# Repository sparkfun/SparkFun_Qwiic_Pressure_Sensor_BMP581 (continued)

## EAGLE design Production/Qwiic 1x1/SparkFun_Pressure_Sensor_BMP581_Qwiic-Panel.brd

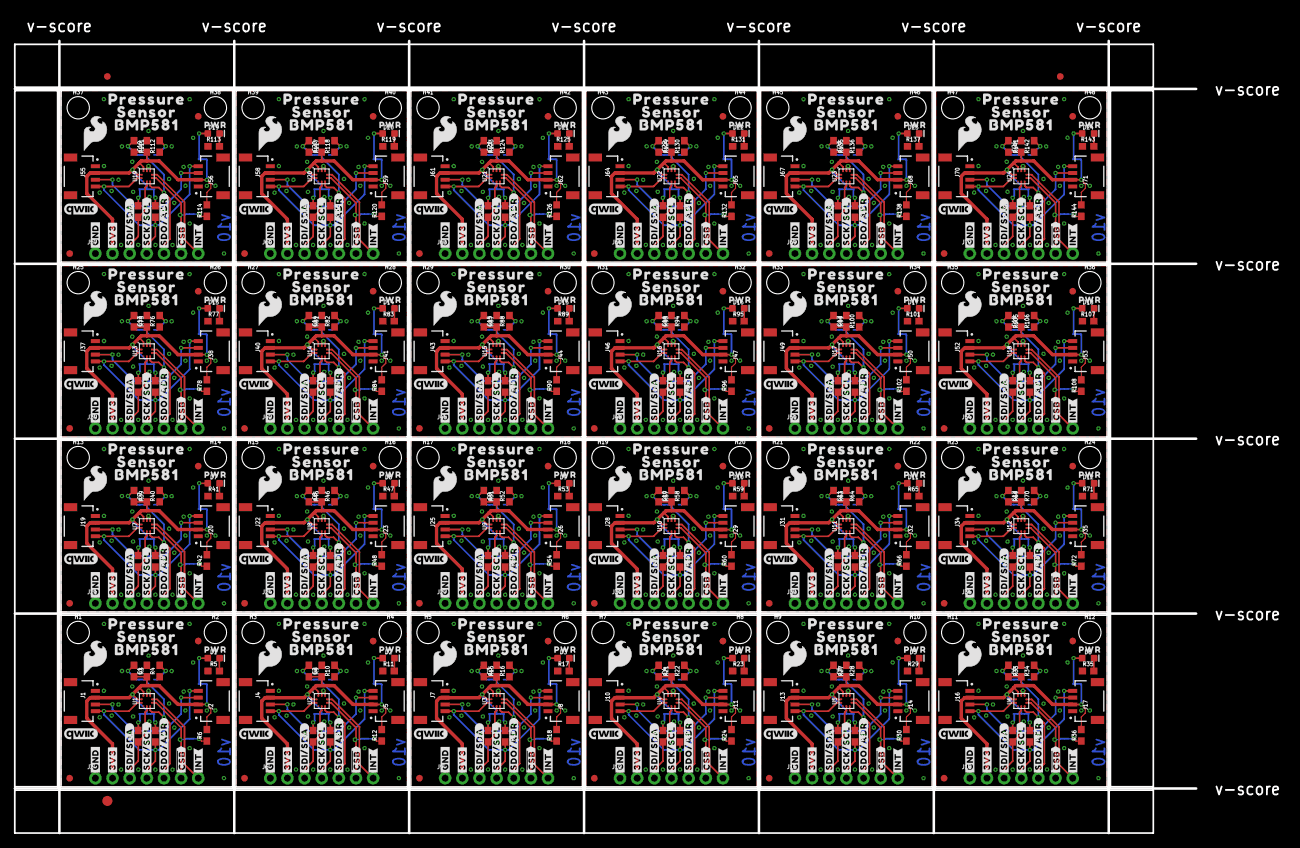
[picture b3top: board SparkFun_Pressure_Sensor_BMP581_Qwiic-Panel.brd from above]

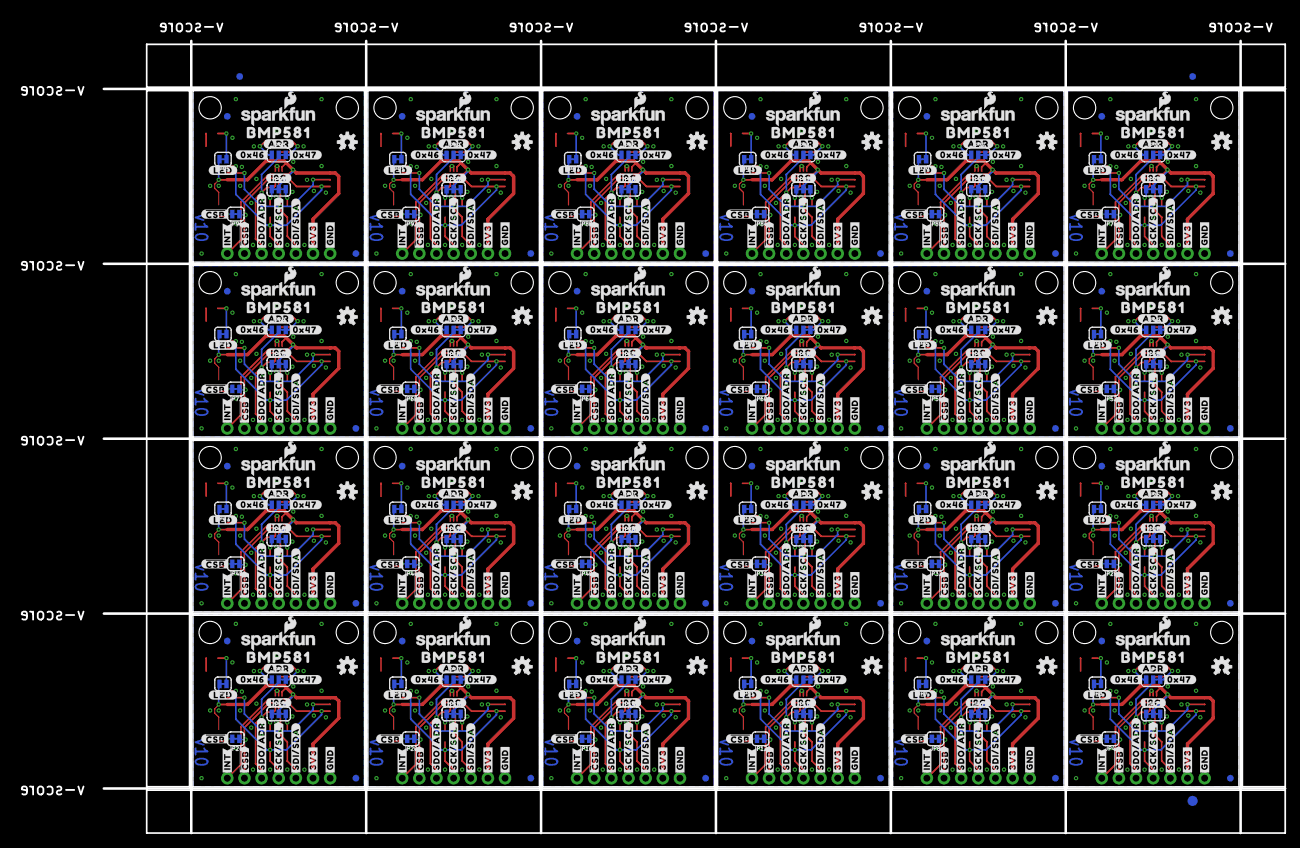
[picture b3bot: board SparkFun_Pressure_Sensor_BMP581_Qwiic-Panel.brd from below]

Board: 2 copper layers, 175.0 x 117.3 mm, 1230 parts (531 on the bottom side), 336 nets.

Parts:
C1, C2, C3, C4, C5, C6, C7, C8, C9, C10, C11, C12, C13, C14, C15, C16, C17, C18, C19, C20, C21, C22, C23, C24: 0.1uF; 0603
D1, D2, D3, D4, D5, D6, D7, D8, D9, D10, D11, D12, D13, D14, D15, D16, D17, D18, D19, D20, D21, D22, D23, D24: RED; LED-0603
E$1, E$2, E$3, E$4: FIDUCIAL-1X2
E$5, E$6: FIDUCIAL-1.5X3
FD1, FD2, FD3, FD4, FD5, FD6, FD7, FD8, FD9, FD10, FD11, FD12, FD13, FD14, FD15, FD16, FD17, FD18, FD19, FD20, FD21, FD22, FD23, FD24, FD25, FD26, FD27, FD28, FD29, FD30, FD31, FD32, FD33, FD34, FD35, FD36, FD37, FD38, FD39, FD40, FD41, FD42, FD43, FD44, FD45, FD46, FD47, FD48, FD49, FD50, FD51, FD52, FD53, FD54, FD55, FD56, FD57, FD58, FD59, FD60, FD61, FD62, FD63, FD64, FD65, FD66, FD67, FD68, FD69, FD70, FD71, FD72, FD73, FD74, FD75, FD76, FD77, FD78, FD79, FD80, FD81, FD82, FD83, FD84, FD85, FD86, FD87, FD88, FD89, FD90, FD91, FD92, FD93, FD94, FD95, FD96: FIDUCIAL1X2; FIDUCIAL-1X2
H1, H2, H3, H4, H5, H6, H7, H8, H9, H10, H11, H12, H13, H14, H15, H16, H17, H18, H19, H20, H21, H22, H23, H24, H25, H26, H27, H28, H29, H30, H31, H32, H33, H34, H35, H36, H37, H38, H39, H40, H41, H42, H43, H44, H45, H46, H47, H48: STAND-OFF
J1, J2, J4, J5, J7, J8, J10, J11, J13, J14, J16, J17, J19, J20, J22, J23, J25, J26, J28, J29, J31, J32, J34, J35, J37, J38, J40, J41, J43, J44, J46, J47, J49, J50, J52, J53, J55, J56, J58, J59, J61, J62, J64, J65, J67, J68, J70, J71: QWIIC_RIGHT_ANGLE; JST04_1MM_RA
J3, J6, J9, J12, J15, J18, J21, J24, J27, J30, J33, J36, J39, J42, J45, J48, J51, J54, J57, J60, J63, J66, J69, J72: 1X07_NO_SILK
JP1, JP5, JP9, JP13, JP17, JP21, JP25, JP29, JP33, JP37, JP41, JP45, JP49, JP53, JP57, JP61, JP65, JP69, JP73, JP77, JP81, JP85, JP89, JP93: ADR; SMT-JUMPER_3_1-NC_TRACE_SILK
JP2, JP6, JP10, JP14, JP18, JP22, JP26, JP30, JP34, JP38, JP42, JP46, JP50, JP54, JP58, JP62, JP66, JP70, JP74, JP78, JP82, JP86, JP90, JP94: I2C; SMT-JUMPER_3_2-NC_TRACE_SILK
JP3, JP7, JP11, JP15, JP19, JP23, JP27, JP31, JP35, JP39, JP43, JP47, JP51, JP55, JP59, JP63, JP67, JP71, JP75, JP79, JP83, JP87, JP91, JP95: LED; SMT-JUMPER_2_NC_TRACE_SILK
JP4, JP8, JP12, JP16, JP20, JP24, JP28, JP32, JP36, JP40, JP44, JP48, JP52, JP56, JP60, JP64, JP68, JP72, JP76, JP80, JP84, JP88, JP92, JP96: !CSB!; SMT-JUMPER_2_NC_TRACE_SILK
LOGO1, LOGO5, LOGO9, LOGO13, LOGO17, LOGO21, LOGO25, LOGO29, LOGO33, LOGO37, LOGO41, LOGO45, LOGO49, LOGO53, LOGO57, LOGO61, LOGO65, LOGO69, LOGO73, LOGO77, LOGO81, LOGO85, LOGO89, LOGO93: OSHW-LOGOS; OSHW-LOGO-S
LOGO2, LOGO6, LOGO10, LOGO14, LOGO18, LOGO22, LOGO26, LOGO30, LOGO34, LOGO38, LOGO42, LOGO46, LOGO50, LOGO54, LOGO58, LOGO62, LOGO66, LOGO70, LOGO74, LOGO78, LOGO82, LOGO86, LOGO90, LOGO94: SFE_LOGO_FLAME.2_INCH; SFE_LOGO_FLAME_.2
LOGO3, LOGO7, LOGO11, LOGO15, LOGO19, LOGO23, LOGO27, LOGO31, LOGO35, LOGO39, LOGO43, LOGO47, LOGO51, LOGO55, LOGO59, LOGO63, LOGO67, LOGO71, LOGO75, LOGO79, LOGO83, LOGO87, LOGO91, LOGO95: QWIIC_LOGO_5MM; QWIIC_5MM
LOGO4, LOGO8, LOGO12, LOGO16, LOGO20, LOGO24, LOGO28, LOGO32, LOGO36, LOGO40, LOGO44, LOGO48, LOGO52, LOGO56, LOGO60, LOGO64, LOGO68, LOGO72, LOGO76, LOGO80, LOGO84, LOGO88, LOGO92, LOGO96: SFE_LOGO_NAME_FLAME.1_INCH; SFE_LOGO_NAME_FLAME_.1
R1, R2, R7, R8, R13, R14, R19, R20, R25, R26, R31, R32, R37, R38, R43, R44, R49, R50, R55, R56, R61, R62, R67, R68, R73, R74, R79, R80, R85, R86, R91, R92, R97, R98, R103, R104, R109, R110, R115, R116, R121, R122, R127, R128, R133, R134, R139, R140: 2.2k; 0603
R3, R4, R6, R9, R10, R12, R15, R16, R18, R21, R22, R24, R27, R28, R30, R33, R34, R36, R39, R40, R42, R45, R46, R48, R51, R52, R54, R57, R58, R60, R63, R64, R66, R69, R70, R72, R75, R76, R78, R81, R82, R84, R87, R88, R90, R93, R94, R96, R99, R100, R102, R105, R106, R108, R111, R112, R114, R117, R118, R120, R123, R124, R126, R129, R130, R132, R135, R136, R138, R141, R142, R144: 10k; 0603
R5, R11, R17, R23, R29, R35, R41, R47, R53, R59, R65, R71, R77, R83, R89, R95, R101, R107, R113, R119, R125, R131, R137, R143: 1k; 0603
U1, U2, U3, U4, U5, U6, U7, U8, U9, U10, U11, U12, U13, U14, U15, U16, U17, U18, U19, U20, U21, U22, U23, U24: BMP581
U$1, U$22, U$27, U$50, U$53, U$75, U$78, U$100, U$103, U$125, U$128, U$150, U$153, U$175, U$178, U$200, U$203, U$225, U$228, U$250, U$253, U$275, U$278, U$300, U$303, U$325, U$328, U$350, U$353, U$375, U$378, U$400, U$403, U$425, U$428, U$450, U$453, U$475, U$478, U$500, U$503, U$525, U$528, U$550, U$553, U$575, U$578, U$600: BMP5810
U$2, U$3, U$29, U$30, U$54, U$55, U$79, U$80, U$104, U$105, U$129, U$130, U$154, U$155, U$179, U$180, U$204, U$205, U$229, U$230, U$254, U$255, U$279, U$280, U$304, U$305, U$329, U$330, U$354, U$355, U$379, U$380, U$404, U$405, U$429, U$430, U$454, U$455, U$479, U$480, U$504, U$505, U$529, U$530, U$554, U$555, U$579, U$580: #GND#0
U$4, U$20, U$39, U$40, U$64, U$65, U$89, U$90, U$114, U$115, U$139, U$140, U$164, U$165, U$189, U$190, U$214, U$215, U$239, U$240, U$264, U$265, U$289, U$290, U$314, U$315, U$339, U$340, U$364, U$365, U$389, U$390, U$414, U$415, U$439, U$440, U$464, U$465, U$489, U$490, U$514, U$515, U$539, U$540, U$564, U$565, U$589, U$590: #3V3#0
U$5, U$6, U$31, U$32, U$56, U$57, U$81, U$82, U$106, U$107, U$131, U$132, U$156, U$157, U$181, U$182, U$206, U$207, U$231, U$232, U$256, U$257, U$281, U$282, U$306, U$307, U$331, U$332, U$356, U$357, U$381, U$382, U$406, U$407, U$431, U$432, U$456, U$457, U$481, U$482, U$506, U$507, U$531, U$532, U$556, U$557, U$581, U$582: #SDI#SDA#0
U$7, U$8, U$33, U$34, U$58, U$59, U$83, U$84, U$108, U$109, U$133, U$134, U$158, U$159, U$183, U$184, U$208, U$209, U$233, U$234, U$258, U$259, U$283, U$284, U$308, U$309, U$333, U$334, U$358, U$359, U$383, U$384, U$408, U$409, U$433, U$434, U$458, U$459, U$483, U$484, U$508, U$509, U$533, U$534, U$558, U$559, U$583, U$584: #SCK#SCL#0
U$9, U$10, U$35, U$36, U$60, U$61, U$85, U$86, U$110, U$111, U$135, U$136, U$160, U$161, U$185, U$186, U$210, U$211, U$235, U$236, U$260, U$261, U$285, U$286, U$310, U$311, U$335, U$336, U$360, U$361, U$385, U$386, U$410, U$411, U$435, U$436, U$460, U$461, U$485, U$486, U$510, U$511, U$535, U$536, U$560, U$561, U$585, U$586: #SDO#ADR#0
U$11, U$45, U$70, U$95, U$120, U$145, U$170, U$195, U$220, U$245, U$270, U$295, U$320, U$345, U$370, U$395, U$420, U$445, U$470, U$495, U$520, U$545, U$570, U$595: #I2C#0
U$12, U$46, U$71, U$96, U$121, U$146, U$171, U$196, U$221, U$246, U$271, U$296, U$321, U$346, U$371, U$396, U$421, U$446, U$471, U$496, U$521, U$546, U$571, U$596: #0X46#0
U$13, U$14, U$37, U$38, U$62, U$63, U$87, U$88, U$112, U$113, U$137, U$138, U$162, U$163, U$187, U$188, U$212, U$213, U$237, U$238, U$262, U$263, U$287, U$288, U$312, U$313, U$337, U$338, U$362, U$363, U$387, U$388, U$412, U$413, U$437, U$438, U$462, U$463, U$487, U$488, U$512, U$513, U$537, U$538, U$562, U$563, U$587, U$588: #INT#0
U$15, U$47, U$72, U$97, U$122, U$147, U$172, U$197, U$222, U$247, U$272, U$297, U$322, U$347, U$372, U$397, U$422, U$447, U$472, U$497, U$522, U$547, U$572, U$597: #0X47#0
U$16, U$48, U$73, U$98, U$123, U$148, U$173, U$198, U$223, U$248, U$273, U$298, U$323, U$348, U$373, U$398, U$423, U$448, U$473, U$498, U$523, U$548, U$573, U$598: PWR0
U$17, U$43, U$68, U$93, U$118, U$143, U$168, U$193, U$218, U$243, U$268, U$293, U$318, U$343, U$368, U$393, U$418, U$443, U$468, U$493, U$518, U$543, U$568, U$593: #ADR#0
U$18, U$49, U$74, U$99, U$124, U$149, U$174, U$199, U$224, U$249, U$274, U$299, U$324, U$349, U$374, U$399, U$424, U$449, U$474, U$499, U$524, U$549, U$574, U$599: ##CSB##1
U$19, U$44, U$69, U$94, U$119, U$144, U$169, U$194, U$219, U$244, U$269, U$294, U$319, U$344, U$369, U$394, U$419, U$444, U$469, U$494, U$519, U$544, U$569, U$594: #LED#0
U$21, U$23, U$51, U$76, U$101, U$126, U$151, U$176, U$201, U$226, U$251, U$276, U$301, U$326, U$351, U$376, U$401, U$426, U$451, U$476, U$501, U$526, U$551, U$576: PRESSURE0
U$24, U$26, U$52, U$77, U$102, U$127, U$152, U$177, U$202, U$227, U$252, U$277, U$302, U$327, U$352, U$377, U$402, U$427, U$452, U$477, U$502, U$527, U$552, U$577: SENSOR0
U$25, U$28, U$41, U$42, U$66, U$67, U$91, U$92, U$116, U$117, U$141, U$142, U$166, U$167, U$191, U$192, U$216, U$217, U$241, U$242, U$266, U$267, U$291, U$292, U$316, U$317, U$341, U$342, U$366, U$367, U$391, U$392, U$416, U$417, U$441, U$442, U$466, U$467, U$491, U$492, U$516, U$517, U$541, U$542, U$566, U$567, U$591, U$592: ##CSB##0

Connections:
!CSB!: J3.6, JP4.1, U1.6
!CSB!1: J6.6, JP8.1, U2.6
!CSB!2: J9.6, JP12.1, U3.6
!CSB!3: J12.6, JP16.1, U4.6
!CSB!4: J15.6, JP20.1, U5.6
!CSB!5: J18.6, JP24.1, U6.6
!CSB!6: J21.6, JP28.1, U7.6
!CSB!7: J24.6, JP32.1, U8.6
!CSB!8: J27.6, JP36.1, U9.6
!CSB!9: J30.6, JP40.1, U10.6
!CSB!10: J33.6, JP44.1, U11.6
!CSB!11: J36.6, JP48.1, U12.6
!CSB!12: J39.6, JP52.1, U13.6
!CSB!13: J42.6, JP56.1, U14.6
!CSB!14: J45.6, JP60.1, U15.6
!CSB!15: J48.6, JP64.1, U16.6
!CSB!16: J51.6, JP68.1, U17.6
!CSB!17: J54.6, JP72.1, U18.6
!CSB!18: J57.6, JP76.1, U19.6
!CSB!19: J60.6, JP80.1, U20.6
!CSB!20: J63.6, JP84.1, U21.6
!CSB!21: J66.6, JP88.1, U22.6
!CSB!22: J69.6, JP92.1, U23.6
!CSB!23: J72.6, JP96.1, U24.6
GND: C1.2, J1.1, J2.1, J3.1, R4.1, R5.1, U1.3, U1.8, U1.9
GND1: C2.2, J4.1, J5.1, J6.1, R10.1, R11.1, U2.3, U2.8, U2.9
GND2: C3.2, J7.1, J8.1, J9.1, R16.1, R17.1, U3.3, U3.8, U3.9
GND3: C4.2, J10.1, J11.1, J12.1, R22.1, R23.1, U4.3, U4.8, U4.9
GND4: C5.2, J13.1, J14.1, J15.1, R28.1, R29.1, U5.3, U5.8, U5.9
GND5: C6.2, J16.1, J17.1, J18.1, R34.1, R35.1, U6.3, U6.8, U6.9
GND6: C7.2, J19.1, J20.1, J21.1, R40.1, R41.1, U7.3, U7.8, U7.9
GND7: C8.2, J22.1, J23.1, J24.1, R46.1, R47.1, U8.3, U8.8, U8.9
GND8: C9.2, J25.1, J26.1, J27.1, R52.1, R53.1, U9.3, U9.8, U9.9
GND9: C10.2, J28.1, J29.1, J30.1, R58.1, R59.1, U10.3, U10.8, U10.9
GND10: C11.2, J31.1, J32.1, J33.1, R64.1, R65.1, U11.3, U11.8, U11.9
GND11: C12.2, J34.1, J35.1, J36.1, R70.1, R71.1, U12.3, U12.8, U12.9
GND12: C13.2, J37.1, J38.1, J39.1, R76.1, R77.1, U13.3, U13.8, U13.9
GND13: C14.2, J40.1, J41.1, J42.1, R82.1, R83.1, U14.3, U14.8, U14.9
GND14: C15.2, J43.1, J44.1, J45.1, R88.1, R89.1, U15.3, U15.8, U15.9
GND15: C16.2, J46.1, J47.1, J48.1, R94.1, R95.1, U16.3, U16.8, U16.9
GND16: C17.2, J49.1, J50.1, J51.1, R100.1, R101.1, U17.3, U17.8, U17.9
GND17: C18.2, J52.1, J53.1, J54.1, R106.1, R107.1, U18.3, U18.8, U18.9
GND18: C19.2, J55.1, J56.1, J57.1, R112.1, R113.1, U19.3, U19.8, U19.9
GND19: C20.2, J58.1, J59.1, J60.1, R118.1, R119.1, U20.3, U20.8, U20.9
GND20: C21.2, J61.1, J62.1, J63.1, R124.1, R125.1, U21.3, U21.8, U21.9
GND21: C22.2, J64.1, J65.1, J66.1, R130.1, R131.1, U22.3, U22.8, U22.9
GND22: C23.2, J67.1, J68.1, J69.1, R136.1, R137.1, U23.3, U23.8, U23.9
GND23: C24.2, J70.1, J71.1, J72.1, R142.1, R143.1, U24.3, U24.8, U24.9
INT: J3.7, U1.7
INT1: J6.7, U2.7
INT2: J9.7, U3.7
INT3: J12.7, U4.7
INT4: J15.7, U5.7
INT5: J18.7, U6.7
INT6: J21.7, U7.7
INT7: J24.7, U8.7
INT8: J27.7, U9.7
INT9: J30.7, U10.7
INT10: J33.7, U11.7
INT11: J36.7, U12.7
INT12: J39.7, U13.7
INT13: J42.7, U14.7
INT14: J45.7, U15.7
INT15: J48.7, U16.7
INT16: J51.7, U17.7
INT17: J54.7, U18.7
INT18: J57.7, U19.7
INT19: J60.7, U20.7
INT20: J63.7, U21.7
INT21: J66.7, U22.7
INT22: J69.7, U23.7
INT23: J72.7, U24.7
unnamed: JP1.3, R3.1
unnamed: JP1.1, R4.2
unnamed: JP2.1, R2.1
unnamed: JP2.3, R1.2
unnamed: D1.A, JP3.1
unnamed: D1.C, R5.2
unnamed: JP4.2, R6.1
unnamed: JP5.3, R9.1
unnamed: JP5.1, R10.2
unnamed: JP6.1, R8.1
unnamed: JP6.3, R7.2
unnamed: D2.A, JP7.1
unnamed: D2.C, R11.2
unnamed: JP8.2, R12.1
unnamed: JP9.3, R15.1
unnamed: JP9.1, R16.2
unnamed: JP10.1, R14.1
unnamed: JP10.3, R13.2
unnamed: D3.A, JP11.1
unnamed: D3.C, R17.2
unnamed: JP12.2, R18.1
unnamed: JP13.3, R21.1
unnamed: JP13.1, R22.2
unnamed: JP14.1, R20.1
unnamed: JP14.3, R19.2
unnamed: D4.A, JP15.1
unnamed: D4.C, R23.2
unnamed: JP16.2, R24.1
unnamed: JP17.3, R27.1
unnamed: JP17.1, R28.2
unnamed: JP18.1, R26.1
unnamed: JP18.3, R25.2
unnamed: D5.A, JP19.1
unnamed: D5.C, R29.2
unnamed: JP20.2, R30.1
unnamed: JP21.3, R33.1
unnamed: JP21.1, R34.2
unnamed: JP22.1, R32.1
unnamed: JP22.3, R31.2
unnamed: D6.A, JP23.1
unnamed: D6.C, R35.2
unnamed: JP24.2, R36.1
unnamed: JP25.3, R39.1
unnamed: JP25.1, R40.2
unnamed: JP26.1, R38.1
unnamed: JP26.3, R37.2
unnamed: D7.A, JP27.1
unnamed: D7.C, R41.2
unnamed: JP28.2, R42.1
unnamed: JP29.3, R45.1
unnamed: JP29.1, R46.2
unnamed: JP30.1, R44.1
unnamed: JP30.3, R43.2
unnamed: D8.A, JP31.1
unnamed: D8.C, R47.2
unnamed: JP32.2, R48.1
unnamed: JP33.3, R51.1
unnamed: JP33.1, R52.2
unnamed: JP34.1, R50.1
unnamed: JP34.3, R49.2
unnamed: D9.A, JP35.1
unnamed: D9.C, R53.2
unnamed: JP36.2, R54.1
unnamed: JP37.3, R57.1
unnamed: JP37.1, R58.2
unnamed: JP38.1, R56.1
unnamed: JP38.3, R55.2
unnamed: D10.A, JP39.1
unnamed: D10.C, R59.2
unnamed: JP40.2, R60.1
unnamed: JP41.3, R63.1
unnamed: JP41.1, R64.2
unnamed: JP42.1, R62.1
unnamed: JP42.3, R61.2
unnamed: D11.A, JP43.1
unnamed: D11.C, R65.2
unnamed: JP44.2, R66.1
unnamed: JP45.3, R69.1
unnamed: JP45.1, R70.2
unnamed: JP46.1, R68.1
unnamed: JP46.3, R67.2
unnamed: D12.A, JP47.1
unnamed: D12.C, R71.2
unnamed: JP48.2, R72.1
unnamed: JP49.3, R75.1
unnamed: JP49.1, R76.2
unnamed: JP50.1, R74.1
unnamed: JP50.3, R73.2
unnamed: D13.A, JP51.1
unnamed: D13.C, R77.2
unnamed: JP52.2, R78.1
unnamed: JP53.3, R81.1
unnamed: JP53.1, R82.2
unnamed: JP54.1, R80.1
unnamed: JP54.3, R79.2
unnamed: D14.A, JP55.1
unnamed: D14.C, R83.2
unnamed: JP56.2, R84.1
unnamed: JP57.3, R87.1
unnamed: JP57.1, R88.2
unnamed: JP58.1, R86.1
unnamed: JP58.3, R85.2
unnamed: D15.A, JP59.1
unnamed: D15.C, R89.2
unnamed: JP60.2, R90.1
unnamed: JP61.3, R93.1
unnamed: JP61.1, R94.2
unnamed: JP62.1, R92.1
unnamed: JP62.3, R91.2
unnamed: D16.A, JP63.1
unnamed: D16.C, R95.2
unnamed: JP64.2, R96.1
unnamed: JP65.3, R99.1
unnamed: JP65.1, R100.2
unnamed: JP66.1, R98.1
unnamed: JP66.3, R97.2
unnamed: D17.A, JP67.1
unnamed: D17.C, R101.2
unnamed: JP68.2, R102.1
unnamed: JP69.3, R105.1
unnamed: JP69.1, R106.2
unnamed: JP70.1, R104.1
unnamed: JP70.3, R103.2
unnamed: D18.A, JP71.1
unnamed: D18.C, R107.2
unnamed: JP72.2, R108.1
unnamed: JP73.3, R111.1
unnamed: JP73.1, R112.2
unnamed: JP74.1, R110.1
unnamed: JP74.3, R109.2
unnamed: D19.A, JP75.1
unnamed: D19.C, R113.2
unnamed: JP76.2, R114.1
unnamed: JP77.3, R117.1
unnamed: JP77.1, R118.2
unnamed: JP78.1, R116.1
unnamed: JP78.3, R115.2
unnamed: D20.A, JP79.1
unnamed: D20.C, R119.2
unnamed: JP80.2, R120.1
unnamed: JP81.3, R123.1
unnamed: JP81.1, R124.2
unnamed: JP82.1, R122.1
unnamed: JP82.3, R121.2
unnamed: D21.A, JP83.1
unnamed: D21.C, R125.2
unnamed: JP84.2, R126.1
unnamed: JP85.3, R129.1
unnamed: JP85.1, R130.2
unnamed: JP86.1, R128.1
unnamed: JP86.3, R127.2
unnamed: D22.A, JP87.1
unnamed: D22.C, R131.2
unnamed: JP88.2, R132.1
unnamed: JP89.3, R135.1
unnamed: JP89.1, R136.2
unnamed: JP90.1, R134.1
unnamed: JP90.3, R133.2
unnamed: D23.A, JP91.1
unnamed: D23.C, R137.2
unnamed: JP92.2, R138.1
unnamed: JP93.3, R141.1
unnamed: JP93.1, R142.2
unnamed: JP94.1, R140.1
unnamed: JP94.3, R139.2
unnamed: D24.A, JP95.1
unnamed: D24.C, R143.2
unnamed: JP96.2, R144.1
SCK/SCL: J1.4, J2.4, J3.4, R2.2, U1.2
SCK/SCL1: J4.4, J5.4, J6.4, R8.2, U2.2
SCK/SCL2: J7.4, J8.4, J9.4, R14.2, U3.2
SCK/SCL3: J10.4, J11.4, J12.4, R20.2, U4.2
SCK/SCL4: J13.4, J14.4, J15.4, R26.2, U5.2
SCK/SCL5: J16.4, J17.4, J18.4, R32.2, U6.2
SCK/SCL6: J19.4, J20.4, J21.4, R38.2, U7.2
SCK/SCL7: J22.4, J23.4, J24.4, R44.2, U8.2
SCK/SCL8: J25.4, J26.4, J27.4, R50.2, U9.2
SCK/SCL9: J28.4, J29.4, J30.4, R56.2, U10.2
SCK/SCL10: J31.4, J32.4, J33.4, R62.2, U11.2
SCK/SCL11: J34.4, J35.4, J36.4, R68.2, U12.2
SCK/SCL12: J37.4, J38.4, J39.4, R74.2, U13.2
SCK/SCL13: J40.4, J41.4, J42.4, R80.2, U14.2
SCK/SCL14: J43.4, J44.4, J45.4, R86.2, U15.2
SCK/SCL15: J46.4, J47.4, J48.4, R92.2, U16.2
SCK/SCL16: J49.4, J50.4, J51.4, R98.2, U17.2
SCK/SCL17: J52.4, J53.4, J54.4, R104.2, U18.2
SCK/SCL18: J55.4, J56.4, J57.4, R110.2, U19.2
SCK/SCL19: J58.4, J59.4, J60.4, R116.2, U20.2
SCK/SCL20: J61.4, J62.4, J63.4, R122.2, U21.2
SCK/SCL21: J64.4, J65.4, J66.4, R128.2, U22.2
SCK/SCL22: J67.4, J68.4, J69.4, R134.2, U23.2
SCK/SCL23: J70.4, J71.4, J72.4, R140.2, U24.2
SDI/SDA: J1.3, J2.3, J3.3, R1.1, U1.4
SDI/SDA1: J4.3, J5.3, J6.3, R7.1, U2.4
SDI/SDA2: J7.3, J8.3, J9.3, R13.1, U3.4
SDI/SDA3: J10.3, J11.3, J12.3, R19.1, U4.4
SDI/SDA4: J13.3, J14.3, J15.3, R25.1, U5.4
SDI/SDA5: J16.3, J17.3, J18.3, R31.1, U6.4
SDI/SDA6: J19.3, J20.3, J21.3, R37.1, U7.4
SDI/SDA7: J22.3, J23.3, J24.3, R43.1, U8.4
SDI/SDA8: J25.3, J26.3, J27.3, R49.1, U9.4
SDI/SDA9: J28.3, J29.3, J30.3, R55.1, U10.4
SDI/SDA10: J31.3, J32.3, J33.3, R61.1, U11.4
SDI/SDA11: J34.3, J35.3, J36.3, R67.1, U12.4
SDI/SDA12: J37.3, J38.3, J39.3, R73.1, U13.4
SDI/SDA13: J40.3, J41.3, J42.3, R79.1, U14.4
SDI/SDA14: J43.3, J44.3, J45.3, R85.1, U15.4
SDI/SDA15: J46.3, J47.3, J48.3, R91.1, U16.4
SDI/SDA16: J49.3, J50.3, J51.3, R97.1, U17.4
SDI/SDA17: J52.3, J53.3, J54.3, R103.1, U18.4
SDI/SDA18: J55.3, J56.3, J57.3, R109.1, U19.4
SDI/SDA19: J58.3, J59.3, J60.3, R115.1, U20.4
SDI/SDA20: J61.3, J62.3, J63.3, R121.1, U21.4
SDI/SDA21: J64.3, J65.3, J66.3, R127.1, U22.4
SDI/SDA22: J67.3, J68.3, J69.3, R133.1, U23.4
SDI/SDA23: J70.3, J71.3, J72.3, R139.1, U24.4
SDO/ADR: J3.5, JP1.2, U1.5
SDO/ADR1: J6.5, JP5.2, U2.5
SDO/ADR2: J9.5, JP9.2, U3.5
SDO/ADR3: J12.5, JP13.2, U4.5
SDO/ADR4: J15.5, JP17.2, U5.5
SDO/ADR5: J18.5, JP21.2, U6.5
SDO/ADR6: J21.5, JP25.2, U7.5
SDO/ADR7: J24.5, JP29.2, U8.5
SDO/ADR8: J27.5, JP33.2, U9.5
SDO/ADR9: J30.5, JP37.2, U10.5
SDO/ADR10: J33.5, JP41.2, U11.5
SDO/ADR11: J36.5, JP45.2, U12.5
SDO/ADR12: J39.5, JP49.2, U13.5
SDO/ADR13: J42.5, JP53.2, U14.5
SDO/ADR14: J45.5, JP57.2, U15.5
SDO/ADR15: J48.5, JP61.2, U16.5
SDO/ADR16: J51.5, JP65.2, U17.5
SDO/ADR17: J54.5, JP69.2, U18.5
SDO/ADR18: J57.5, JP73.2, U19.5
SDO/ADR19: J60.5, JP77.2, U20.5
SDO/ADR20: J63.5, JP81.2, U21.5
SDO/ADR21: J66.5, JP85.2, U22.5
SDO/ADR22: J69.5, JP89.2, U23.5
SDO/ADR23: J72.5, JP93.2, U24.5
VDD: C1.1, J1.2, J2.2, J3.2, JP2.2, JP3.2, R3.2, R6.2, U1.1, U1.10
VDD1: C2.1, J4.2, J5.2, J6.2, JP6.2, JP7.2, R9.2, R12.2, U2.1, U2.10
VDD2: C3.1, J7.2, J8.2, J9.2, JP10.2, JP11.2, R15.2, R18.2, U3.1, U3.10
VDD3: C4.1, J10.2, J11.2, J12.2, JP14.2, JP15.2, R21.2, R24.2, U4.1, U4.10
VDD4: C5.1, J13.2, J14.2, J15.2, JP18.2, JP19.2, R27.2, R30.2, U5.1, U5.10
VDD5: C6.1, J16.2, J17.2, J18.2, JP22.2, JP23.2, R33.2, R36.2, U6.1, U6.10
VDD6: C7.1, J19.2, J20.2, J21.2, JP26.2, JP27.2, R39.2, R42.2, U7.1, U7.10
VDD7: C8.1, J22.2, J23.2, J24.2, JP30.2, JP31.2, R45.2, R48.2, U8.1, U8.10
VDD8: C9.1, J25.2, J26.2, J27.2, JP34.2, JP35.2, R51.2, R54.2, U9.1, U9.10
VDD9: C10.1, J28.2, J29.2, J30.2, JP38.2, JP39.2, R57.2, R60.2, U10.1, U10.10
VDD10: C11.1, J31.2, J32.2, J33.2, JP42.2, JP43.2, R63.2, R66.2, U11.1, U11.10
VDD11: C12.1, J34.2, J35.2, J36.2, JP46.2, JP47.2, R69.2, R72.2, U12.1, U12.10
VDD12: C13.1, J37.2, J38.2, J39.2, JP50.2, JP51.2, R75.2, R78.2, U13.1, U13.10
VDD13: C14.1, J40.2, J41.2, J42.2, JP54.2, JP55.2, R81.2, R84.2, U14.1, U14.10
VDD14: C15.1, J43.2, J44.2, J45.2, JP58.2, JP59.2, R87.2, R90.2, U15.1, U15.10
VDD15: C16.1, J46.2, J47.2, J48.2, JP62.2, JP63.2, R93.2, R96.2, U16.1, U16.10
VDD16: C17.1, J49.2, J50.2, J51.2, JP66.2, JP67.2, R99.2, R102.2, U17.1, U17.10
VDD17: C18.1, J52.2, J53.2, J54.2, JP70.2, JP71.2, R105.2, R108.2, U18.1, U18.10
VDD18: C19.1, J55.2, J56.2, J57.2, JP74.2, JP75.2, R111.2, R114.2, U19.1, U19.10
VDD19: C20.1, J58.2, J59.2, J60.2, JP78.2, JP79.2, R117.2, R120.2, U20.1, U20.10
VDD20: C21.1, J61.2, J62.2, J63.2, JP82.2, JP83.2, R123.2, R126.2, U21.1, U21.10
VDD21: C22.1, J64.2, J65.2, J66.2, JP86.2, JP87.2, R129.2, R132.2, U22.1, U22.10
VDD22: C23.1, J67.2, J68.2, J69.2, JP90.2, JP91.2, R135.2, R138.2, U23.1, U23.10
VDD23: C24.1, J70.2, J71.2, J72.2, JP94.2, JP95.2, R141.2, R144.2, U24.1, U24.10

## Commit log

2022-05-24 Add .gitignore
2022-05-24 Add datasheet
2022-05-24 Create library file for BMP581
2022-05-24 Create 1x1 board
    Copied from BMP384
2022-05-24 Create Micro board
    Copied from BMP384
2022-05-25 Design review updates
    Rename files
    Change to v10 (accelerating to reds)
    Fix sensor name in schematic
    Add note to schematic about max wire diameter in Micro PTH connectors
    Update VDD range
    Fix acid trap in Micro
2022-05-25 Checklist update
2022-05-25 Add 1x1 panel
2022-05-25 Add Micro panel
2022-05-26 Add optional pullup on CSB
2022-05-26 Rename CSB pullup jumper in schematic
2022-05-26 Connect CSB of Micro board to VDD
2022-05-26 Add proto gerbers for 1x1 and Micro
2022-06-09 Design review updates
    Change INT label to fishtail in Micro silk
    Add product name to bottom in 1x1 silk
    Change Micro net labels to be I2C only
    Approve DRC overlaps
    Fix acid trap
    Add note about CSB being tied high in Micro schematic
2022-06-09 Add production files for reds
2022-06-29 Update README.md
    Updating README.md with product info & links.
2022-07-12 Update README.md
    Adding product photo.
2022-07-21 Update README.md
    Updating for Micro release.
2022-07-25 Update README
    Adding Qwiic Micro BMP581 photo.
2022-07-27 Create LICENSE.md
    Adding SparkFun License.md file.
2023-03-28 Remove library file
    BMP384 is in SFE Eagle library, update part in design
